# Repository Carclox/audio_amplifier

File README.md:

# audio_amplifier
Amplificador de audio basado en ejemplos de libro small single audio desing

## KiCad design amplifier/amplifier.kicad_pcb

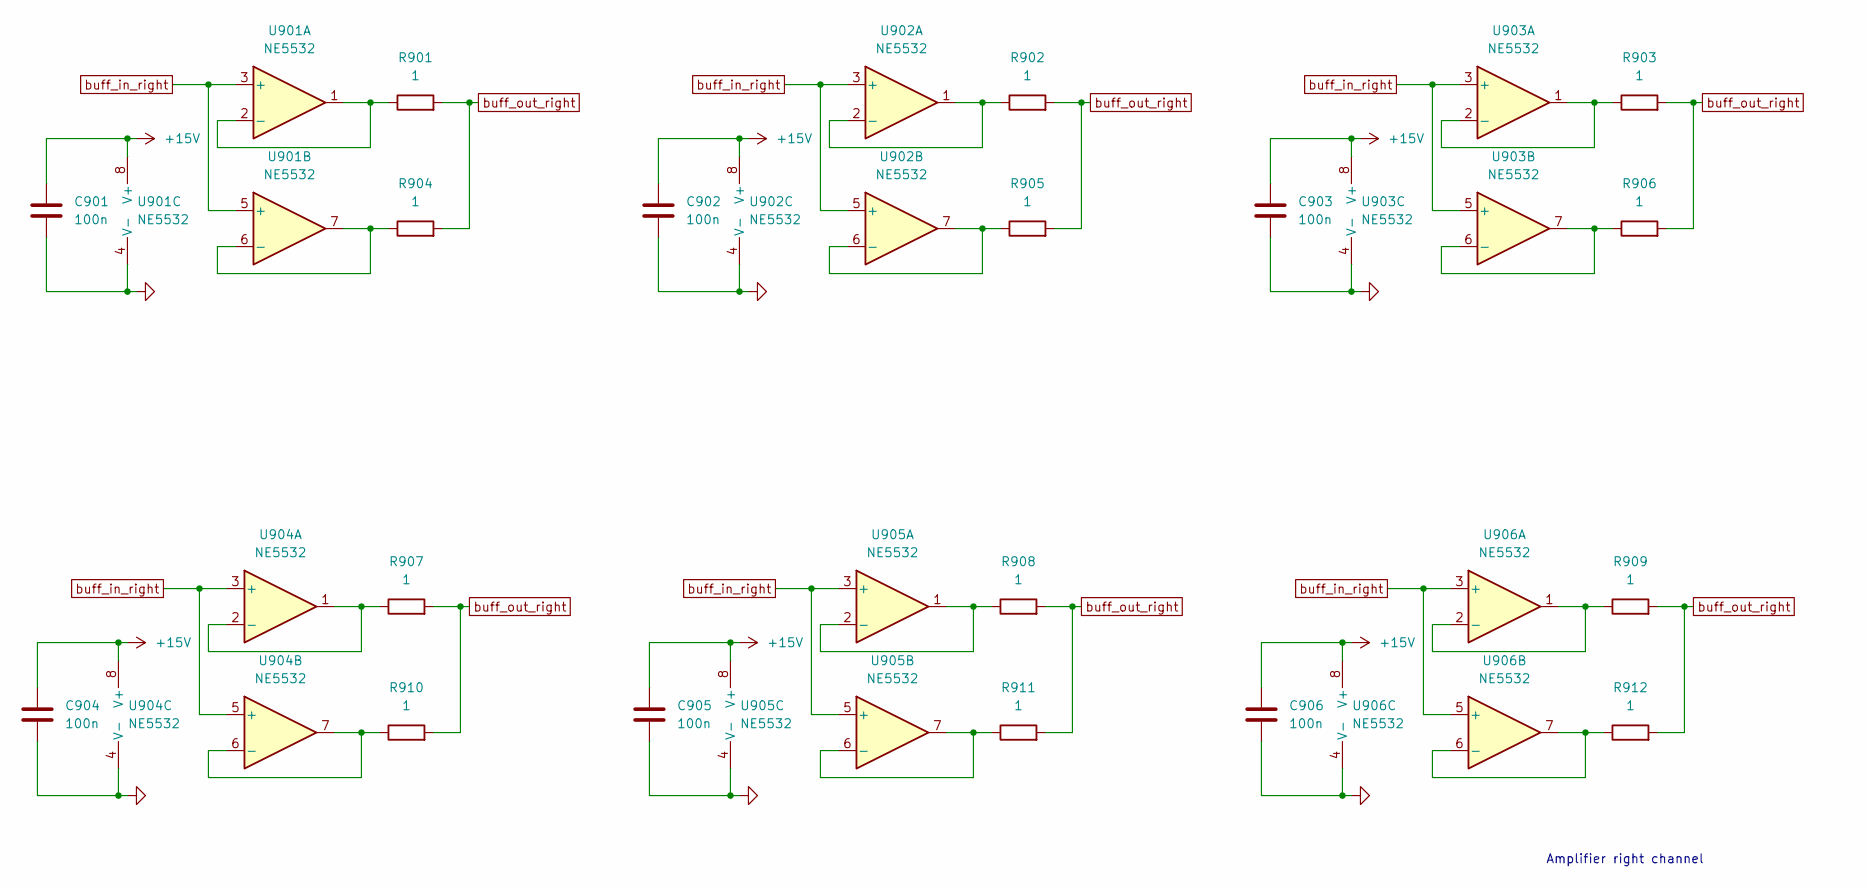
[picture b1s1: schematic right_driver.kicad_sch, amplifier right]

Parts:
C901, C902, C903, C904, C905, C906: 100n; C_0805_2012Metric
R901, R902, R903, R904, R905, R906, R907, R908, R909, R910, R911, R912: 1; R_0805_2012Metric
U901, U902, U903, U904, U905, U906: NE5532; SOIC-8_3.9x4.9mm_P1.27mm

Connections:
+15V: C901.1, C902.1, C903.1, C904.1, C905.1, C906.1, U901.8 (V+), U902.8 (V+), U903.8 (V+), U904.8 (V+), U905.8 (V+), U906.8 (V+); also elsewhere on the board
GND: C901.2, C902.2, C903.2, C904.2, C905.2, C906.2, U901.4 (V-), U902.4 (V-), U903.4 (V-), U904.4 (V-), U905.4 (V-), U906.4 (V-); also elsewhere on the board
unnamed: R901.1, U901.1, U901.2 (-)
unnamed: R904.1, U901.6 (-), U901.7
unnamed: R902.1, U902.1, U902.2 (-)
unnamed: R905.1, U902.6 (-), U902.7
unnamed: R903.1, U903.1, U903.2 (-)
unnamed: R906.1, U903.6 (-), U903.7
unnamed: R907.1, U904.1, U904.2 (-)
unnamed: R910.1, U904.6 (-), U904.7
unnamed: R908.1, U905.1, U905.2 (-)
unnamed: R911.1, U905.6 (-), U905.7
unnamed: R909.1, U906.1, U906.2 (-)
unnamed: R912.1, U906.6 (-), U906.7
buff_in_right: U901.3 (+), U901.5 (+), U902.3 (+), U902.5 (+), U903.3 (+), U903.5 (+), U904.3 (+), U904.5 (+), U905.3 (+), U905.5 (+), U906.3 (+), U906.5 (+); also elsewhere on the board
buff_out_right: R901.2, R902.2, R903.2, R904.2, R905.2, R906.2, R907.2, R908.2, R909.2, R910.2, R911.2, R912.2; also elsewhere on the board

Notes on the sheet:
Amplifier right channel

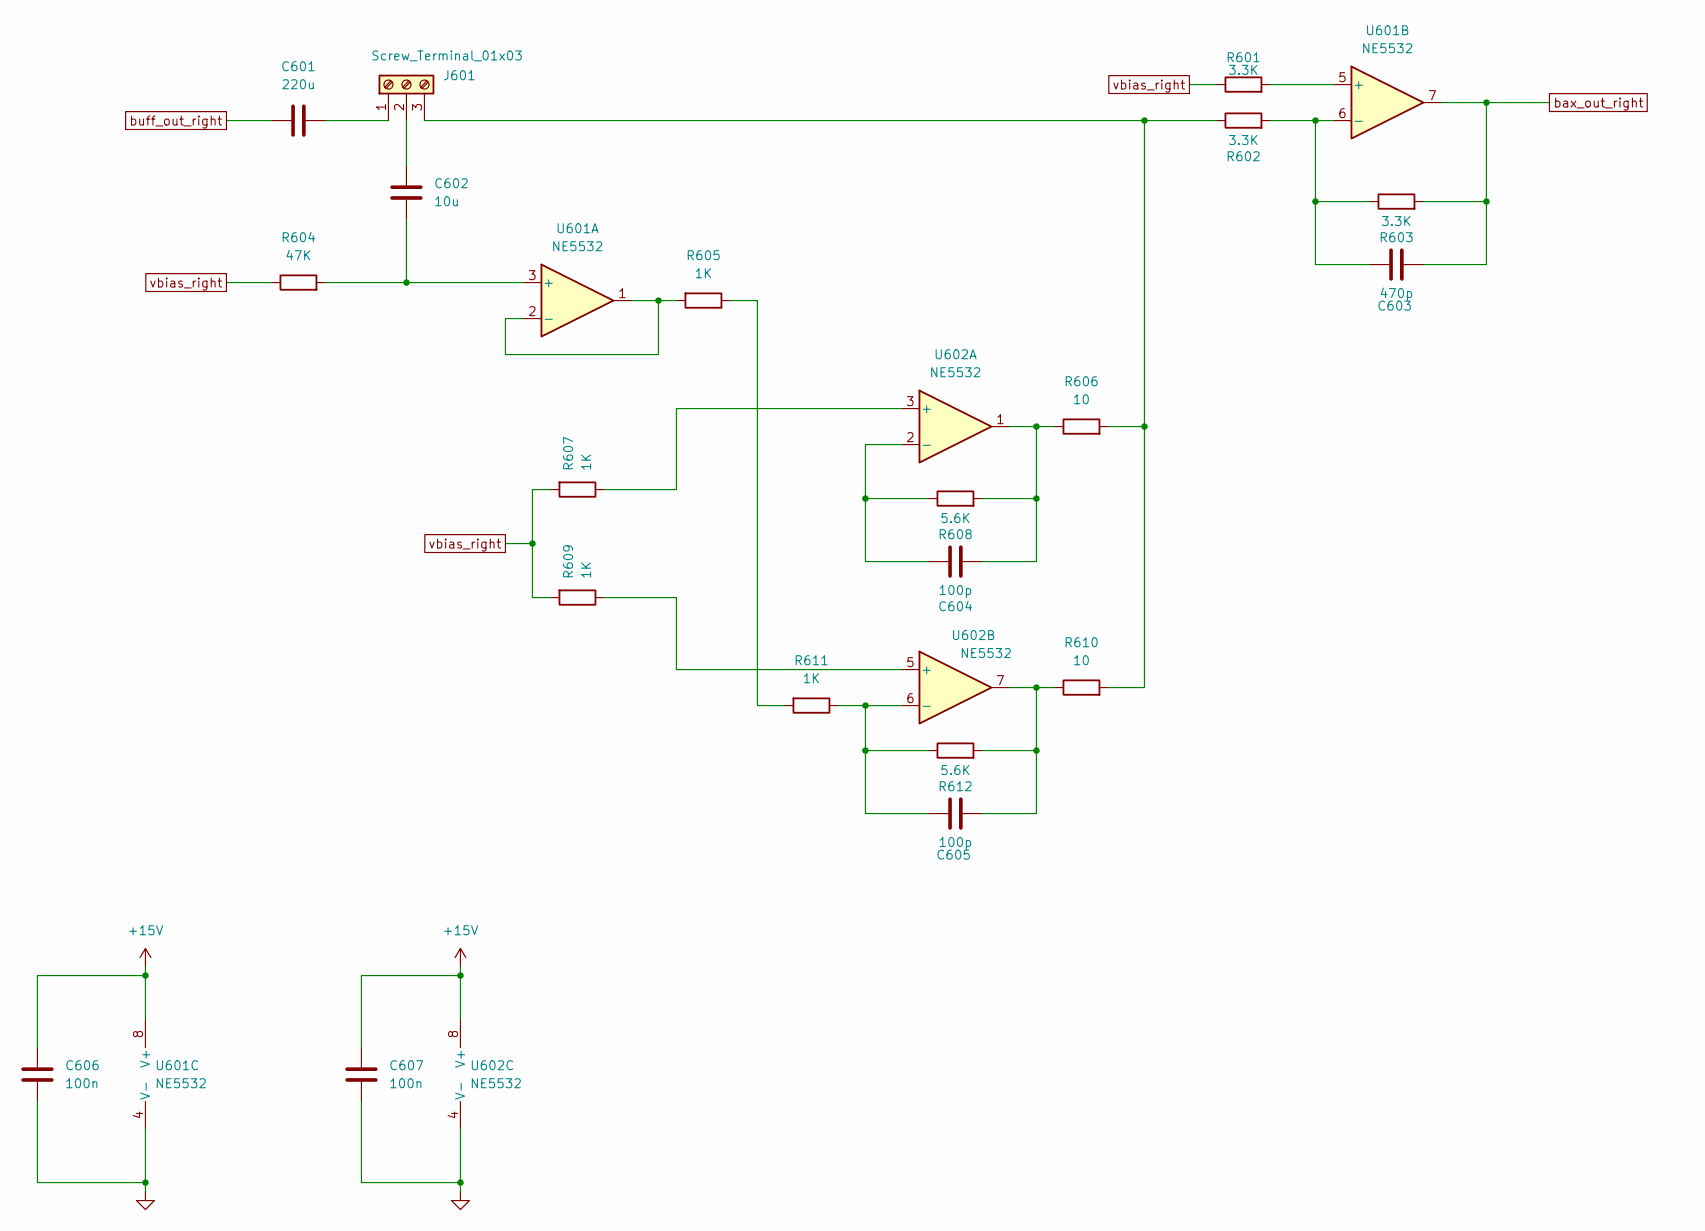
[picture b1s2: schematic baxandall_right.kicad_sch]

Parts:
C601: 220u; C_0805_2012Metric
C602: 10u; C_0805_2012Metric
C603: 470p; C_0805_2012Metric
C604, C605: 100p; C_0805_2012Metric
C606, C607: 100n; C_0805_2012Metric
J601: Screw_Terminal_01x03; TerminalBlock_Altech_AK300-3_P5.00mm
R601, R602, R603: 3.3K; R_0805_2012Metric
R604: 47K; R_0805_2012Metric
R605, R607, R609, R611: 1K; R_0805_2012Metric
R606, R610: 10; R_0805_2012Metric
R608, R612: 5.6K; R_0805_2012Metric
U601, U602: NE5532; SOIC-8_3.9x4.9mm_P1.27mm

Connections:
+15V: C606.1, C607.1, U601.8 (V+), U602.8 (V+); also elsewhere on the board
GND: C606.2, C607.2, U601.4 (V-), U602.4 (V-); also elsewhere on the board
unnamed: C604.2, R606.1, R608.2, U602.1
unnamed: C605.2, R610.1, R612.2, U602.7
unnamed: C601.2, J601.1
unnamed: C602.2, J601.2
unnamed: J601.3, R602.1, R606.2, R610.2
unnamed: R605.1, R611.2
unnamed: C602.1, R604.2, U601.3 (+)
unnamed: R605.2, U601.1, U601.2 (-)
unnamed: R601.2, U601.5 (+)
unnamed: C603.1, R602.2, R603.1, U601.6 (-)
unnamed: R607.1, U602.3 (+)
unnamed: C604.1, R608.1, U602.2 (-)
unnamed: R609.1, U602.5 (+)
unnamed: C605.1, R611.1, R612.1, U602.6 (-)
bax_out_right: C603.2, R603.2, U601.7; also elsewhere on the board
buff_out_right: C601.1; also elsewhere on the board
vbias_right: R601.1, R604.1, R607.2, R609.2; also elsewhere on the board

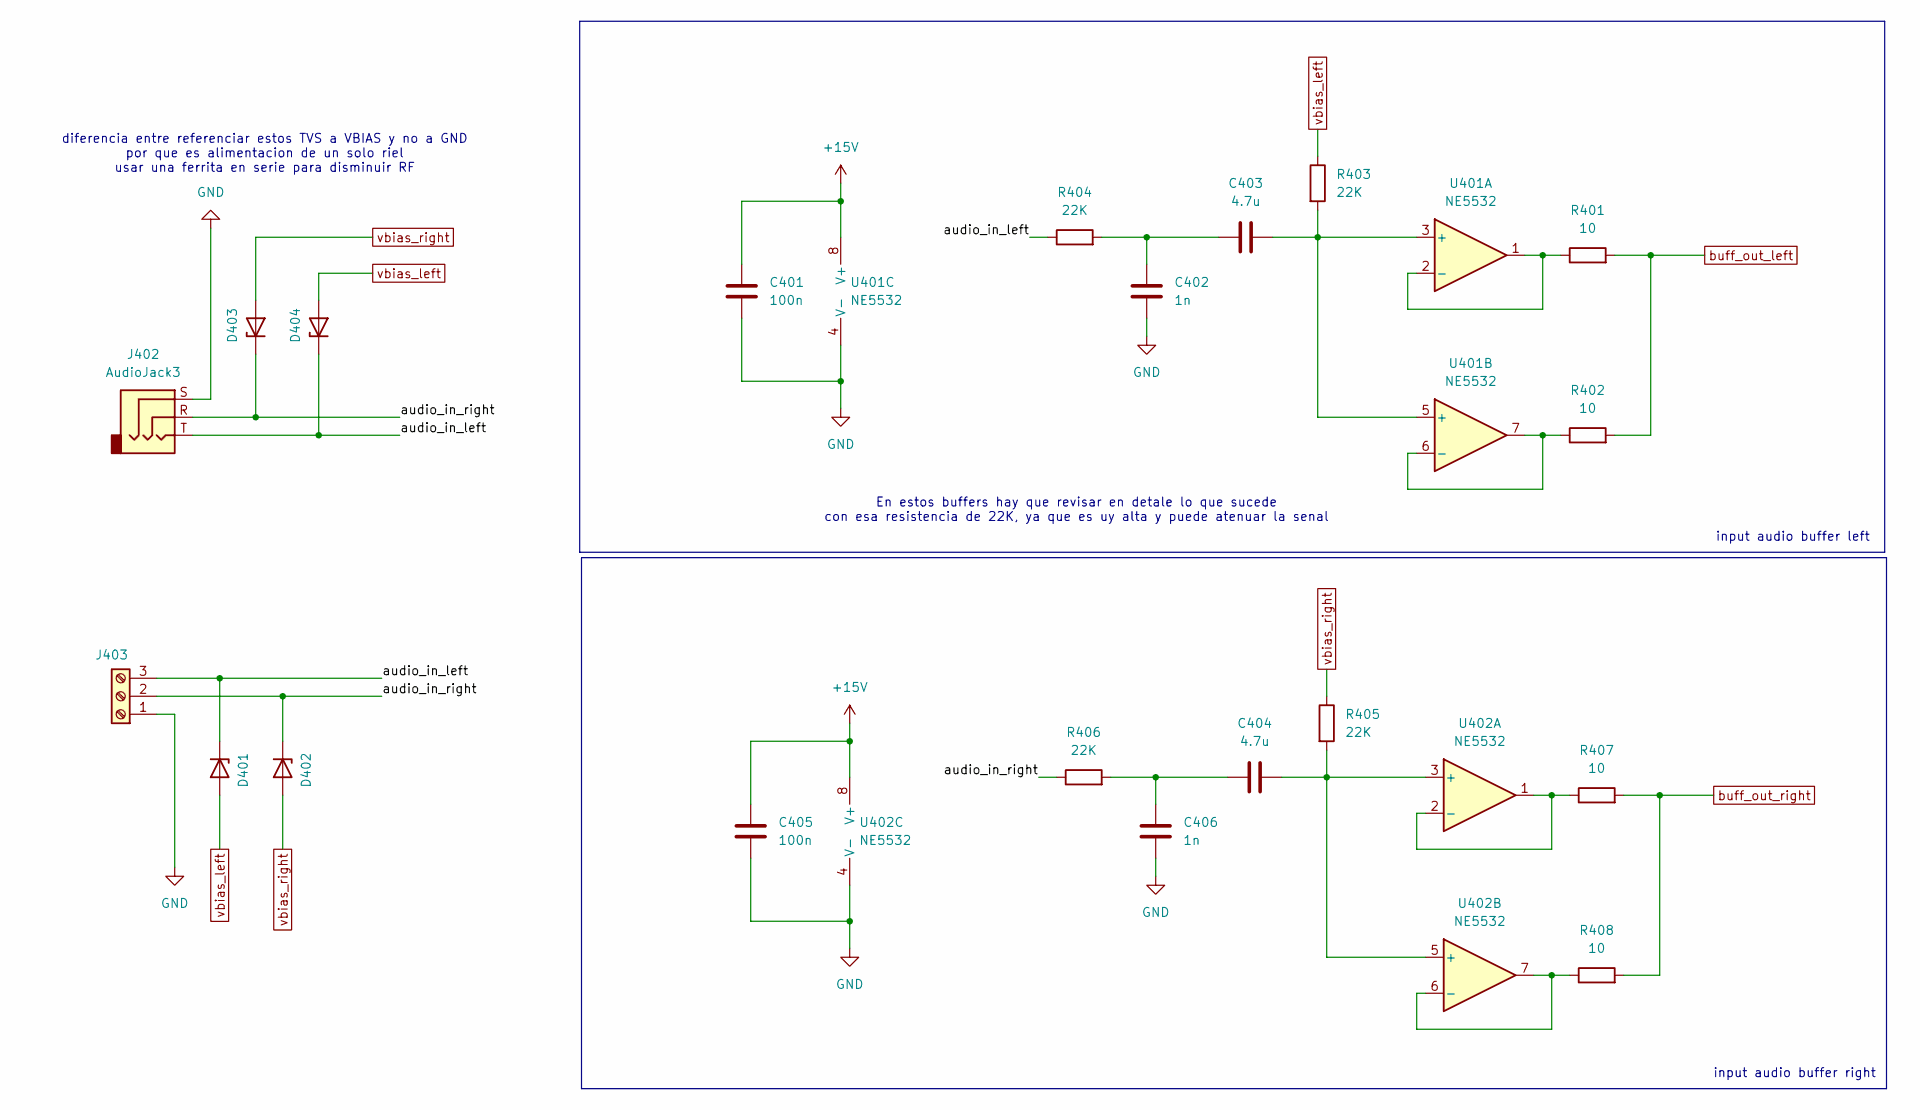
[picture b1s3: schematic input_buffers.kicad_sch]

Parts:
C401, C405: 100n; C_0805_2012Metric
C402, C406: 1n; C_0805_2012Metric
C403, C404: 4.7u; C_0805_2012Metric
D401, D402, D403, D404: PTVS20VZ1USK; Nexperia_DSN1608-2_1.6x0.8mm
J402: AudioJack3; Jack_3.5mm_CUI_SJ-3523-SMT_Horizontal
J403: Screw_Terminal_01x03; TerminalBlock_Altech_AK300-3_P5.00mm
R401, R402, R407, R408: 10; R_0805_2012Metric
R403, R404, R405, R406: 22K; R_0805_2012Metric
U401, U402: NE5532; SOIC-8_3.9x4.9mm_P1.27mm

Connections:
+15V: C401.1, C405.1, U401.8 (V+), U402.8 (V+); also elsewhere on the board
/input_buffers/audio_in_left: D401.1 (K), D404.1 (K), J402.T, J403.3, R404.1
/input_buffers/audio_in_right: D402.1 (K), D403.1 (K), J402.R, J403.2, R406.1
GND: C401.2, C402.2, C405.2, C406.2, J402.S, J403.1, U401.4 (V-), U402.4 (V-); also elsewhere on the board
unnamed: C402.1, C403.1, R404.2
unnamed: C404.1, C406.1, R406.2
unnamed: C403.2, R403.2, U401.3 (+), U401.5 (+)
unnamed: R401.1, U401.1, U401.2 (-)
unnamed: R402.1, U401.6 (-), U401.7
unnamed: C404.2, R405.2, U402.3 (+), U402.5 (+)
unnamed: R407.1, U402.1, U402.2 (-)
unnamed: R408.1, U402.6 (-), U402.7
buff_out_left: R401.2, R402.2; also elsewhere on the board
buff_out_right: R407.2, R408.2; also elsewhere on the board
vbias_left: D401.2 (A), D404.2 (A), R403.1; also elsewhere on the board
vbias_right: D402.2 (A), D403.2 (A), R405.1; also elsewhere on the board

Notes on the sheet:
input audio buffer right
input audio buffer left
En estos buffers hay que revisar en detale lo que sucede con esa resistencia de 22K, ya que es uy alta y puede atenuar la senal
diferencia entre referenciar estos TVS a VBIAS y no a GND por que es alimentacion de un solo riel usar una ferrita en serie para disminuir RF

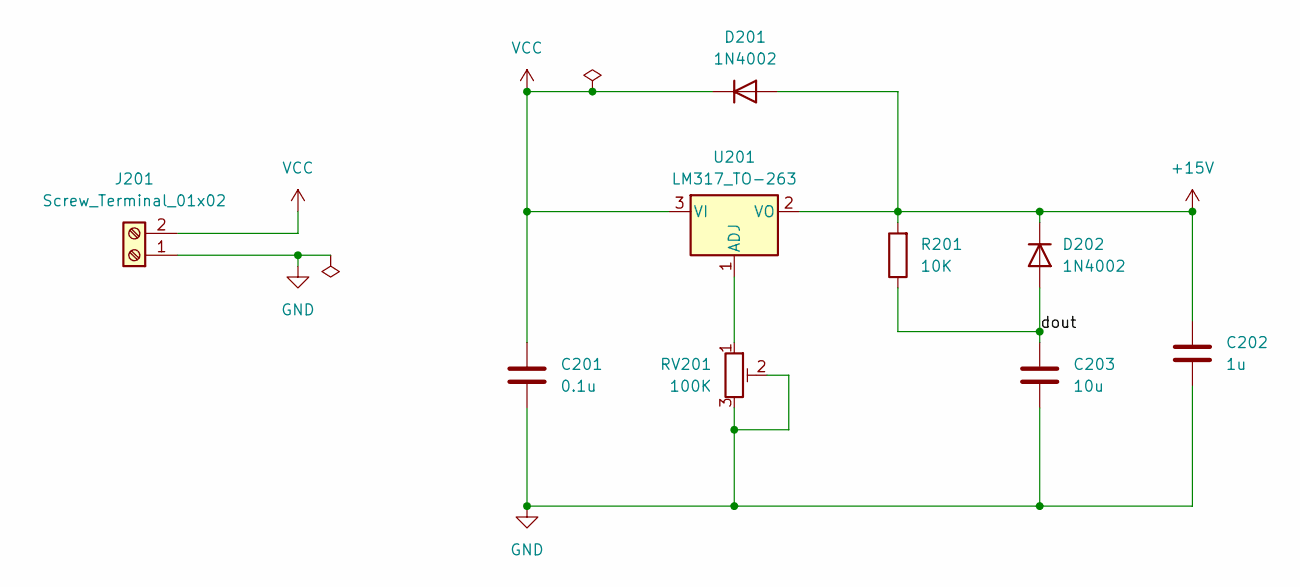
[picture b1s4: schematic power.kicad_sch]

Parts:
C201: 0.1u; C_0805_2012Metric
C202: 1u; C_0805_2012Metric
C203: 10u; C_1210_3225Metric
D201, D202: 1N4002; D_DO-41_SOD81_P10.16mm_Horizontal
J201: Screw_Terminal_01x02; Altech_AK100_1x02_P5.00mm
R201: 10K; R_0805_2012Metric
RV201: 100K; Potentiometer_Bourns_3299W_Vertical
U201: LM317_TO-263; TO-263-3_TabPin2

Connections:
+15V: C202.2, D201.2 (A), D202.1 (K), R201.2, U201.2 (VO); also elsewhere on the board
/power/dout: C203.2, D202.2 (A), R201.1
GND: C201.1, C202.1, C203.1, J201.1, RV201.2, RV201.3; also elsewhere on the board
unnamed: RV201.1, U201.1 (ADJ)
VCC: C201.2, D201.1 (K), J201.2, U201.3 (VI)

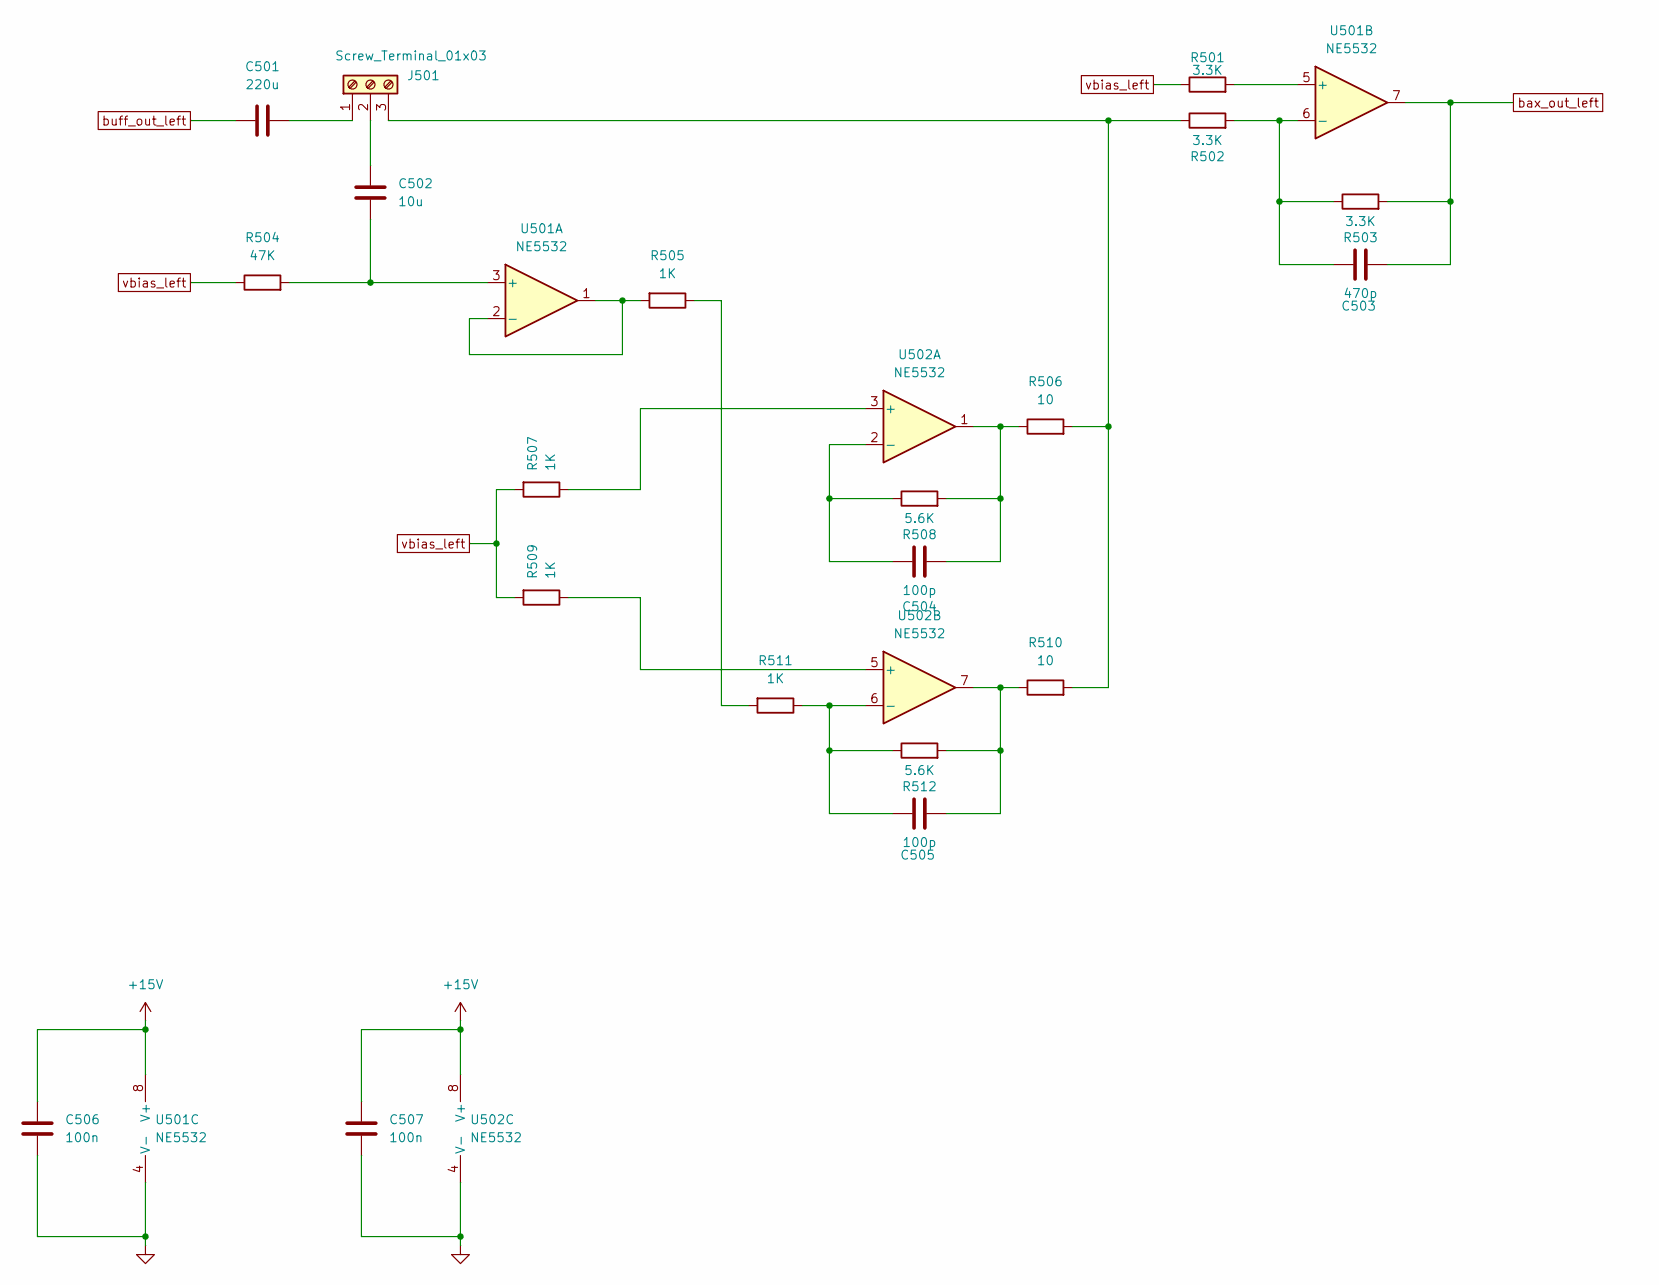
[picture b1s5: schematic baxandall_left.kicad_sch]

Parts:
C501: 220u; C_0805_2012Metric
C502: 10u; C_0805_2012Metric
C503: 470p; C_0805_2012Metric
C504, C505: 100p; C_0805_2012Metric
C506, C507: 100n; C_0805_2012Metric
J501: Screw_Terminal_01x03; TerminalBlock_Altech_AK300-3_P5.00mm
R501, R502, R503: 3.3K; R_0805_2012Metric
R504: 47K; R_0805_2012Metric
R505, R507, R509, R511: 1K; R_0805_2012Metric
R506, R510: 10; R_0805_2012Metric
R508, R512: 5.6K; R_0805_2012Metric
U501, U502: NE5532; SOIC-8_3.9x4.9mm_P1.27mm

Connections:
+15V: C506.1, C507.1, U501.8 (V+), U502.8 (V+); also elsewhere on the board
GND: C506.2, C507.2, U501.4 (V-), U502.4 (V-); also elsewhere on the board
unnamed: C504.2, R506.1, R508.2, U502.1
unnamed: C505.2, R510.1, R512.2, U502.7
unnamed: C501.2, J501.1
unnamed: C502.2, J501.2
unnamed: J501.3, R502.1, R506.2, R510.2
unnamed: R505.1, R511.2
unnamed: C502.1, R504.2, U501.3 (+)
unnamed: R505.2, U501.1, U501.2 (-)
unnamed: R501.2, U501.5 (+)
unnamed: C503.1, R502.2, R503.1, U501.6 (-)
unnamed: R507.1, U502.3 (+)
unnamed: C504.1, R508.1, U502.2 (-)
unnamed: R509.1, U502.5 (+)
unnamed: C505.1, R511.1, R512.1, U502.6 (-)
bax_out_left: C503.2, R503.2, U501.7; also elsewhere on the board
buff_out_left: C501.1; also elsewhere on the board
vbias_left: R501.1, R504.1, R507.2, R509.2; also elsewhere on the board

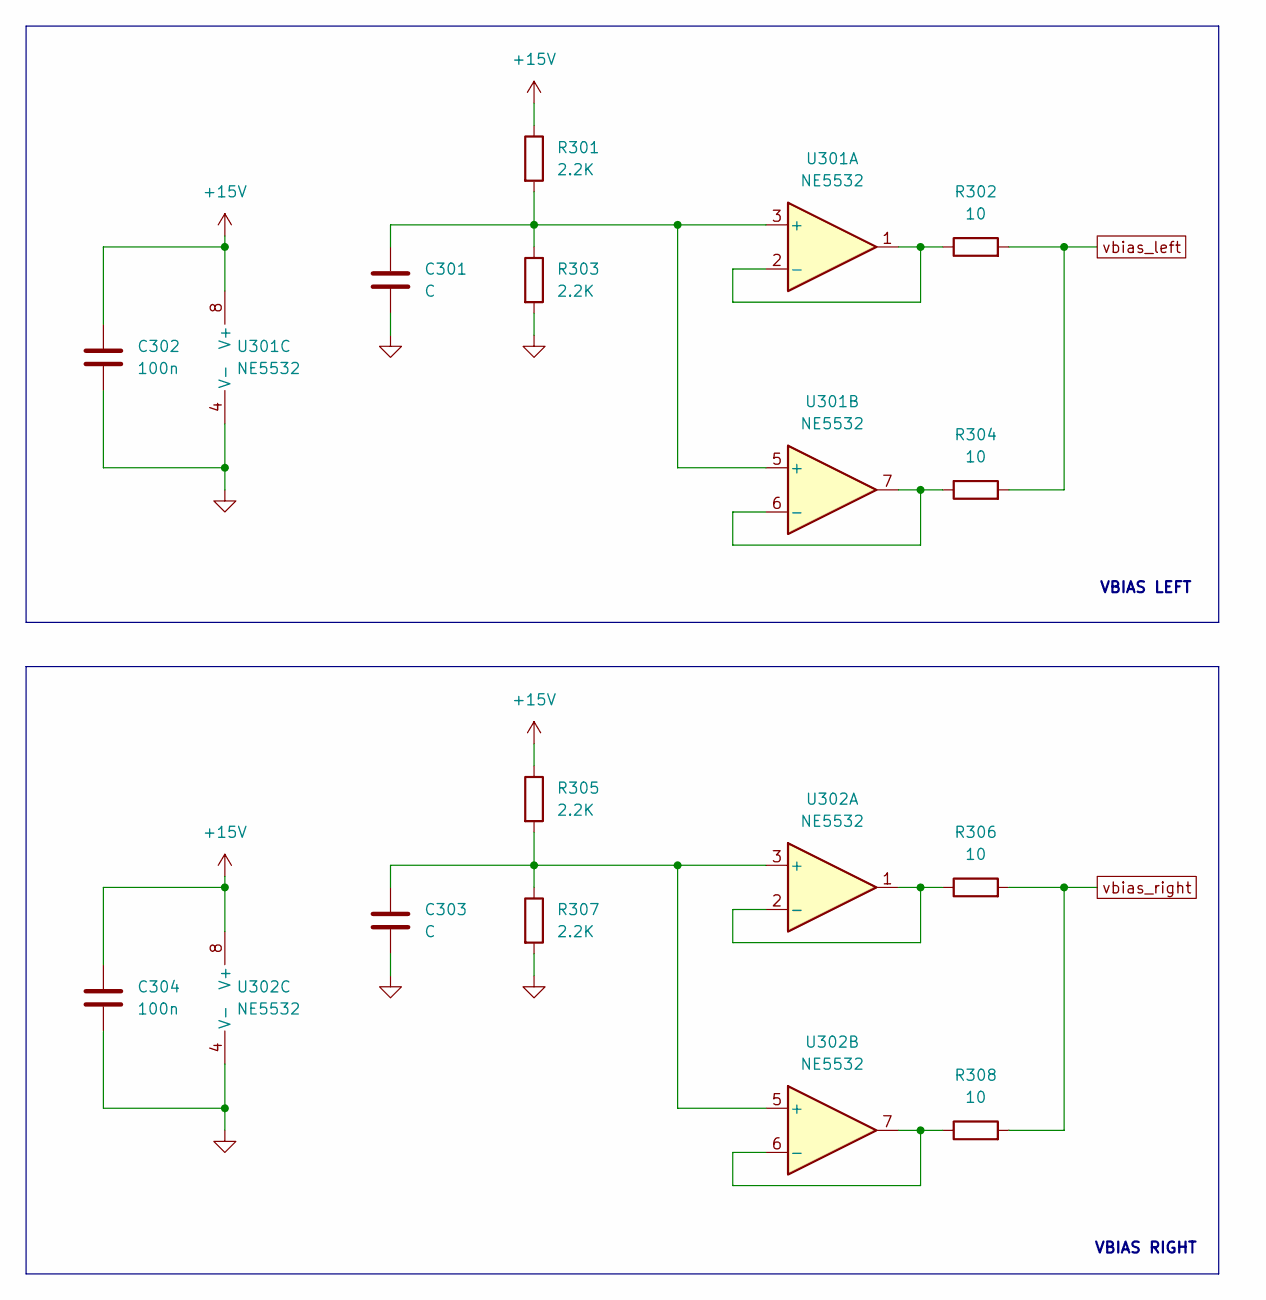
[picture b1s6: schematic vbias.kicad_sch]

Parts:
C301, C303: C; C_Elec_5x5.4
C302, C304: 100n; C_0805_2012Metric
R301, R303, R305, R307: 2.2K; R_0805_2012Metric
R302, R304, R306, R308: 10; R_0805_2012Metric
U301, U302: NE5532; SOIC-8_3.9x4.9mm_P1.27mm

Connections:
+15V: C302.1, C304.1, R301.1, R305.1, U301.8 (V+), U302.8 (V+); also elsewhere on the board
GND: C301.2, C302.2, C303.2, C304.2, R303.2, R307.2, U301.4 (V-), U302.4 (V-); also elsewhere on the board
unnamed: C301.1, R301.2, R303.1, U301.3 (+), U301.5 (+)
unnamed: R302.1, U301.1, U301.2 (-)
unnamed: R304.1, U301.6 (-), U301.7
unnamed: C303.1, R305.2, R307.1, U302.3 (+), U302.5 (+)
unnamed: R306.1, U302.1, U302.2 (-)
unnamed: R308.1, U302.6 (-), U302.7
vbias_left: R302.2, R304.2; also elsewhere on the board
vbias_right: R306.2, R308.2; also elsewhere on the board

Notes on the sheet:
VBIAS RIGHT
VBIAS LEFT

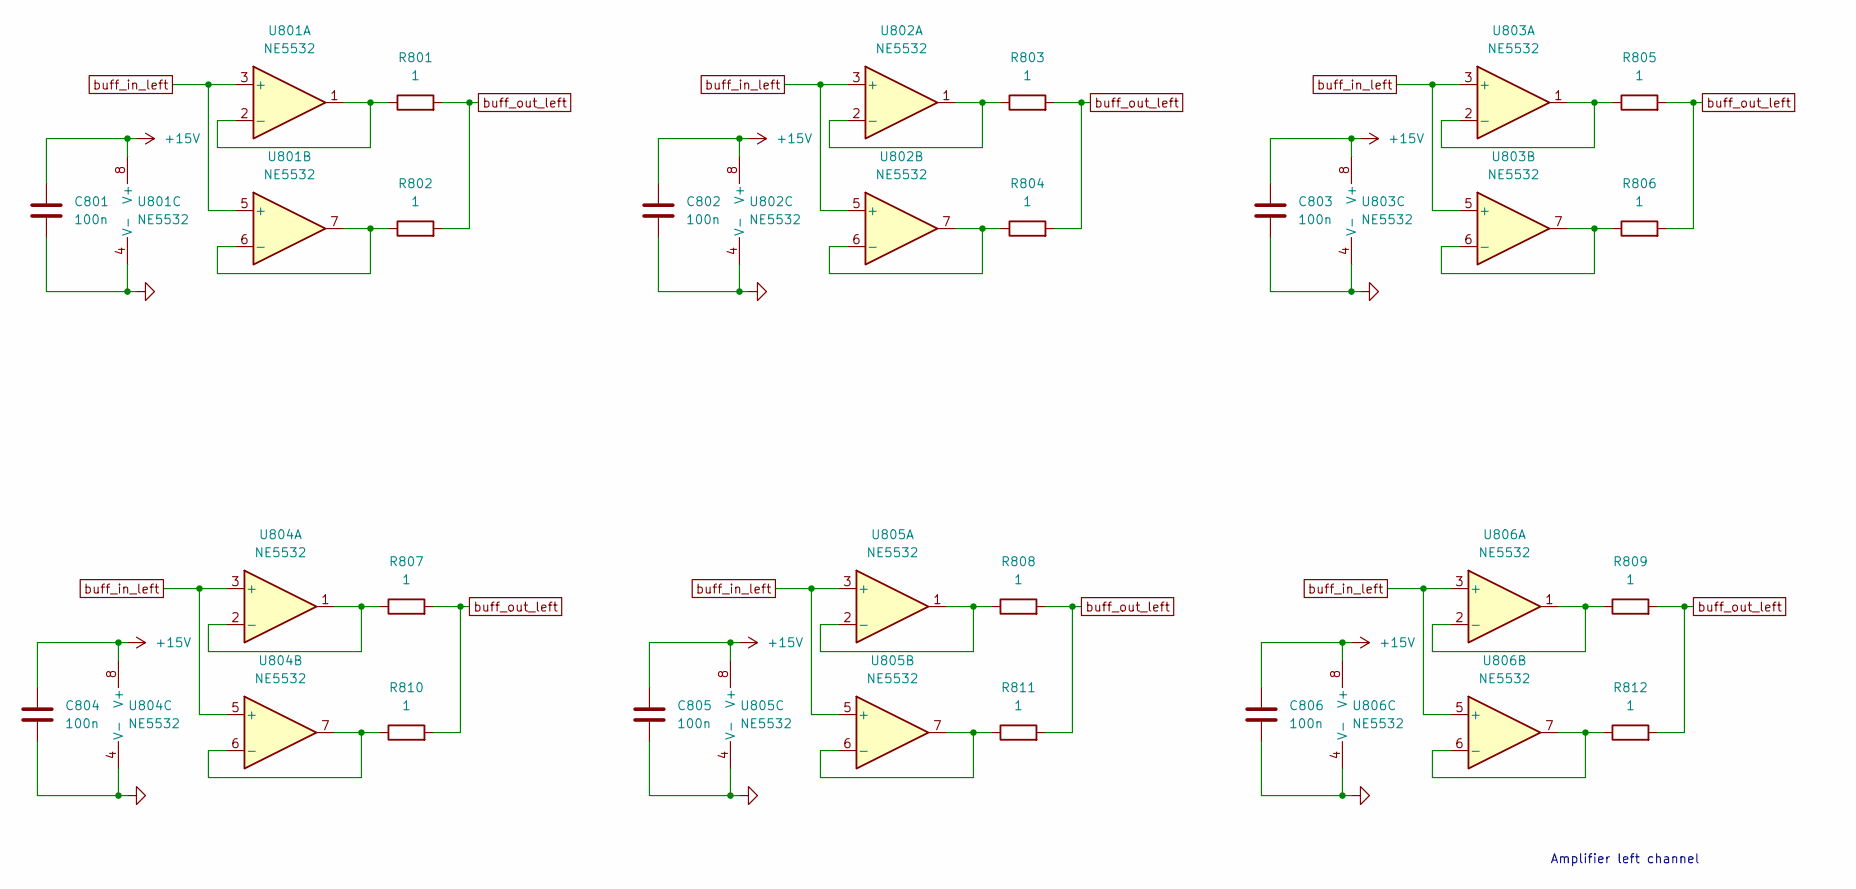
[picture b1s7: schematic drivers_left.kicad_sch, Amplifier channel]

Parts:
C801, C802, C803, C804, C805, C806: 100n; C_0805_2012Metric
R801, R802, R803, R804, R805, R806, R807, R808, R809, R810, R811, R812: 1; R_0805_2012Metric
U801, U802, U803, U804, U805, U806: NE5532; SOIC-8_3.9x4.9mm_P1.27mm

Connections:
+15V: C801.1, C802.1, C803.1, C804.1, C805.1, C806.1, U801.8 (V+), U802.8 (V+), U803.8 (V+), U804.8 (V+), U805.8 (V+), U806.8 (V+); also elsewhere on the board
GND: C801.2, C802.2, C803.2, C804.2, C805.2, C806.2, U801.4 (V-), U802.4 (V-), U803.4 (V-), U804.4 (V-), U805.4 (V-), U806.4 (V-); also elsewhere on the board
unnamed: R801.1, U801.1, U801.2 (-)
unnamed: R802.1, U801.6 (-), U801.7
unnamed: R803.1, U802.1, U802.2 (-)
unnamed: R804.1, U802.6 (-), U802.7
unnamed: R805.1, U803.1, U803.2 (-)
unnamed: R806.1, U803.6 (-), U803.7
unnamed: R807.1, U804.1, U804.2 (-)
unnamed: R810.1, U804.6 (-), U804.7
unnamed: R808.1, U805.1, U805.2 (-)
unnamed: R811.1, U805.6 (-), U805.7
unnamed: R809.1, U806.1, U806.2 (-)
unnamed: R812.1, U806.6 (-), U806.7
buff_in_left: U801.3 (+), U801.5 (+), U802.3 (+), U802.5 (+), U803.3 (+), U803.5 (+), U804.3 (+), U804.5 (+), U805.3 (+), U805.5 (+), U806.3 (+), U806.5 (+); also elsewhere on the board
buff_out_left: R801.2, R802.2, R803.2, R804.2, R805.2, R806.2, R807.2, R808.2, R809.2, R810.2, R811.2, R812.2; also elsewhere on the board

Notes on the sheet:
Amplifier left channel

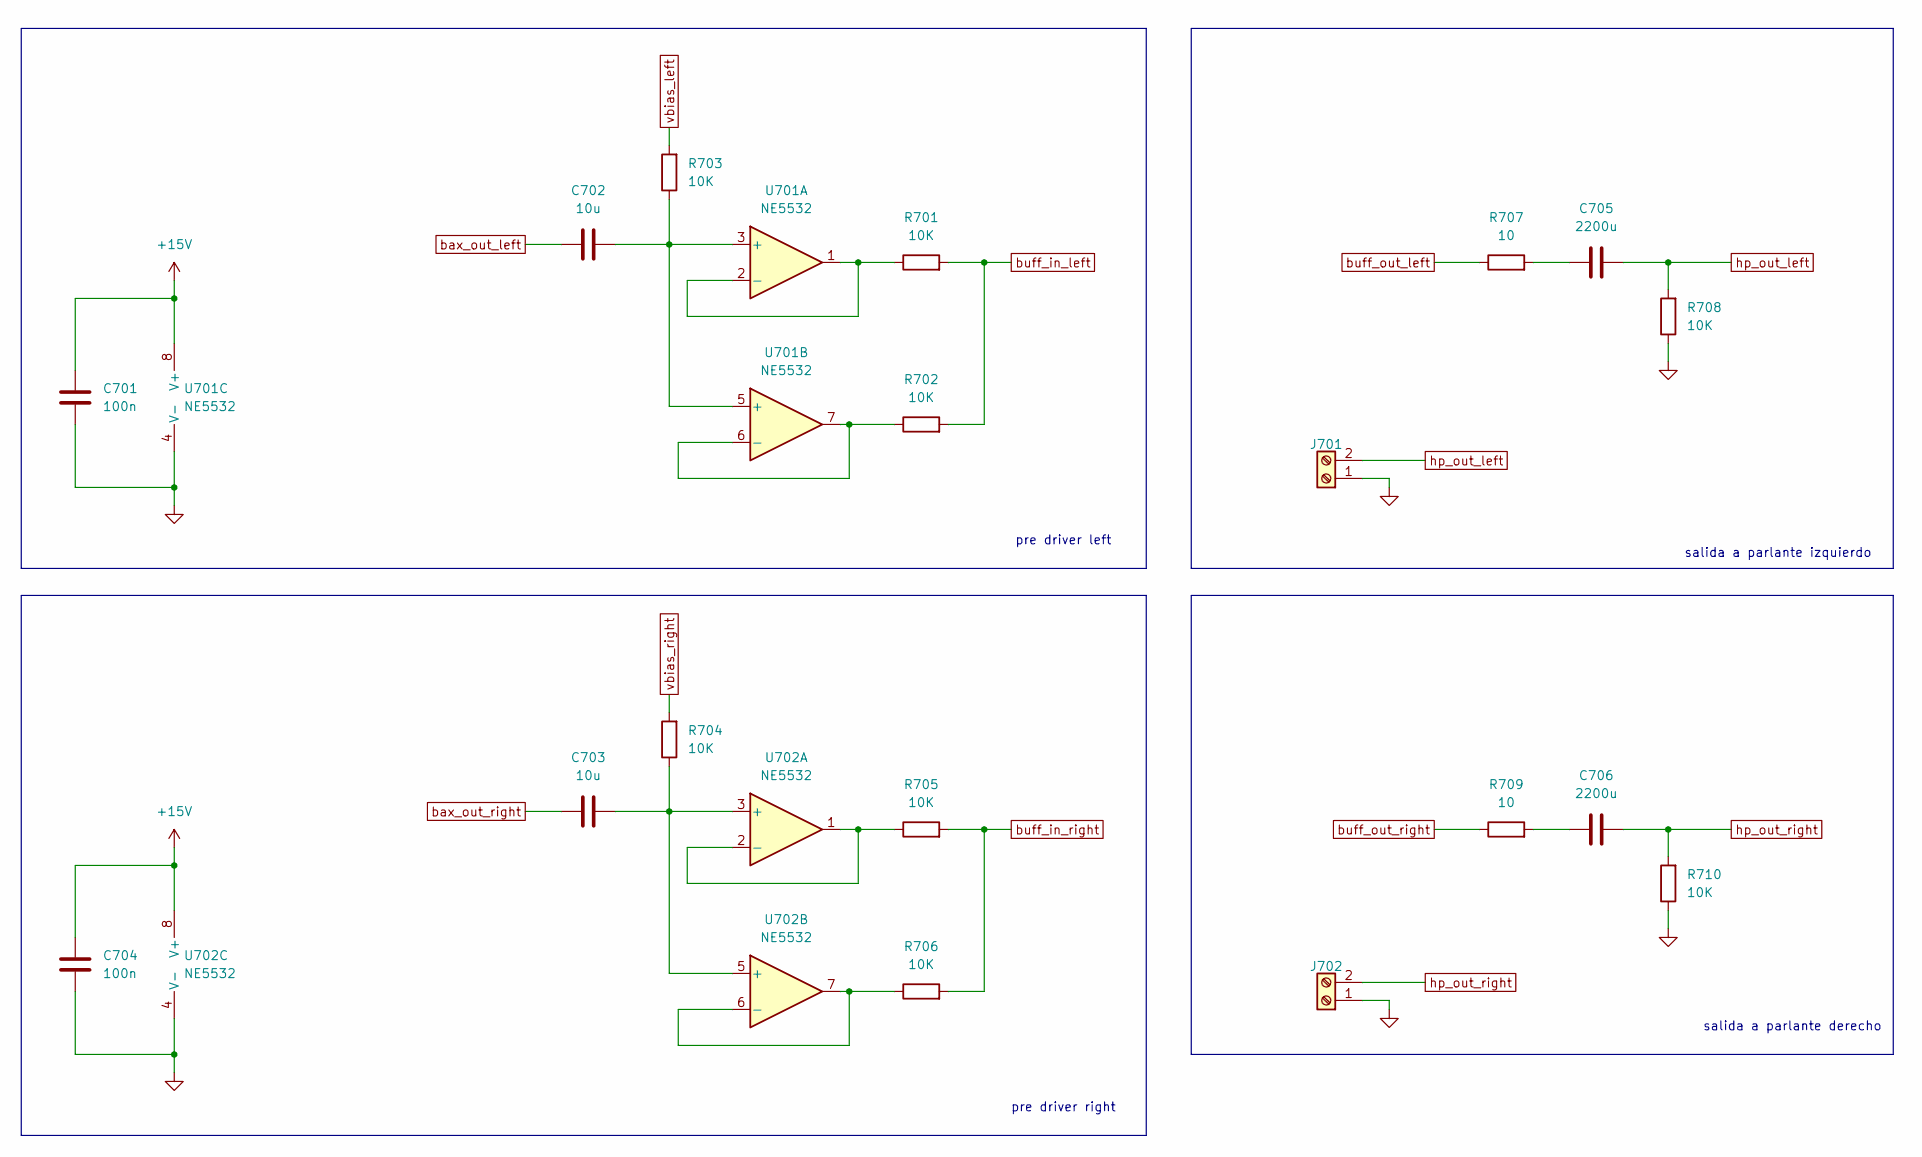
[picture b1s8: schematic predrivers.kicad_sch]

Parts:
C701, C704: 100n; C_0805_2012Metric
C702, C703: 10u; C_0805_2012Metric
C705, C706: 2200u; C_Radial_D16.0mm_H31.5mm_P7.50mm
J701, J702: Screw_Terminal_01x02; TerminalBlock_Altech_AK300-2_P5.00mm
R701, R702, R703, R704, R705, R706, R708, R710: 10K; R_0805_2012Metric
R707, R709: 10; R_0805_2012Metric
U701, U702: NE5532; SOIC-8_3.9x4.9mm_P1.27mm

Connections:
+15V: C701.1, C704.1, U701.8 (V+), U702.8 (V+); also elsewhere on the board
GND: C701.2, C704.2, J701.1, J702.1, R708.1, R710.1, U701.4 (V-), U702.4 (V-); also elsewhere on the board
unnamed: C705.1, R707.2
unnamed: C706.1, R709.2
unnamed: C702.2, R703.1, U701.3 (+), U701.5 (+)
unnamed: R701.1, U701.1, U701.2 (-)
unnamed: R702.1, U701.6 (-), U701.7
unnamed: C703.2, R704.1, U702.3 (+), U702.5 (+)
unnamed: R705.1, U702.1, U702.2 (-)
unnamed: R706.1, U702.6 (-), U702.7
bax_out_left: C702.1; also elsewhere on the board
bax_out_right: C703.1; also elsewhere on the board
buff_in_left: R701.2, R702.2; also elsewhere on the board
buff_in_right: R705.2, R706.2; also elsewhere on the board
buff_out_left: R707.1; also elsewhere on the board
buff_out_right: R709.1; also elsewhere on the board
hp_out_left: C705.2, J701.2, R708.2
hp_out_right: C706.2, J702.2, R710.2
vbias_left: R703.2; also elsewhere on the board
vbias_right: R704.2; also elsewhere on the board

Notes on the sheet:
salida a parlante derecho
pre driver left
salida a parlante izquierdo
pre driver right

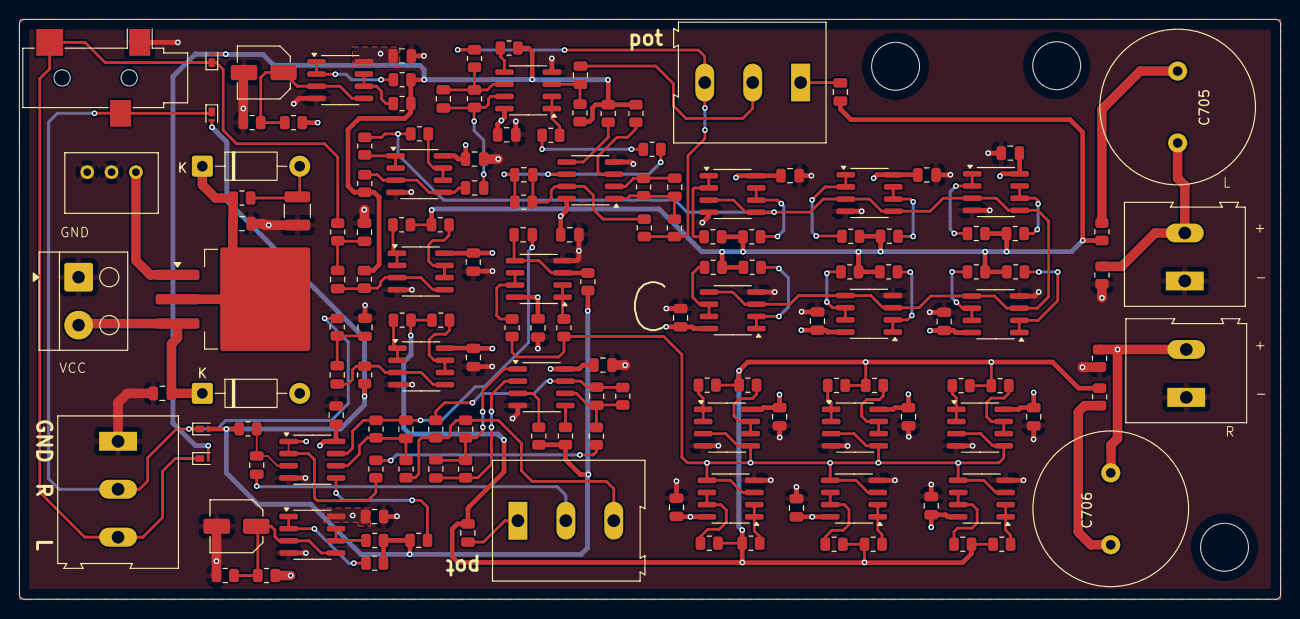
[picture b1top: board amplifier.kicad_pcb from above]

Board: 4 copper layers, 131.6 x 60.5 mm, 157 parts (0 on the bottom side), 91 nets.

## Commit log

2025-09-01 primer version PCB
2025-09-01 drill files and gerber files
2025-09-01 PDFs
2025-09-01 ajustes archivos
2025-09-01 Ignorar carpeta amplifier-backups
